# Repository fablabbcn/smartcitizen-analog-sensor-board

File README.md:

# SmartCitizen Analog Sensor Boards

This repository contains a set of boards that can interface the Smart Citizen Kit in different ways.

The SmartCitizen ASB is an expansion board for the [Smart Citizen Kit](https://github.com/fablabbcn/smartcitizen-kit-21) that provides connectivity to analog sensors with a high precission ADS1115 via I2C, with four configurable addresses. Daisy chainable up to 4 boards (or 2 in 8ch version) - with a total of 16 analog channels.

|Variant|# of Channels|External AREF needed|ADS format|
|:-:|:-:|:-:|:-:|
|4-channel|4|Y|SMD or [shield by adafruit](https://www.adafruit.com/product/1085)|
|8-channel-step|8|N|SMD|

## Characteristics

### Operating voltage

Natively operates at 3.3V, but can use also up to 5.5V in EXT-V, and with a selectable jumper. It integrates a level-shifter from the GROVE connector's voltage to EXT-V.

### Connectivity

I2C, from 3.3V up to 5.5V.

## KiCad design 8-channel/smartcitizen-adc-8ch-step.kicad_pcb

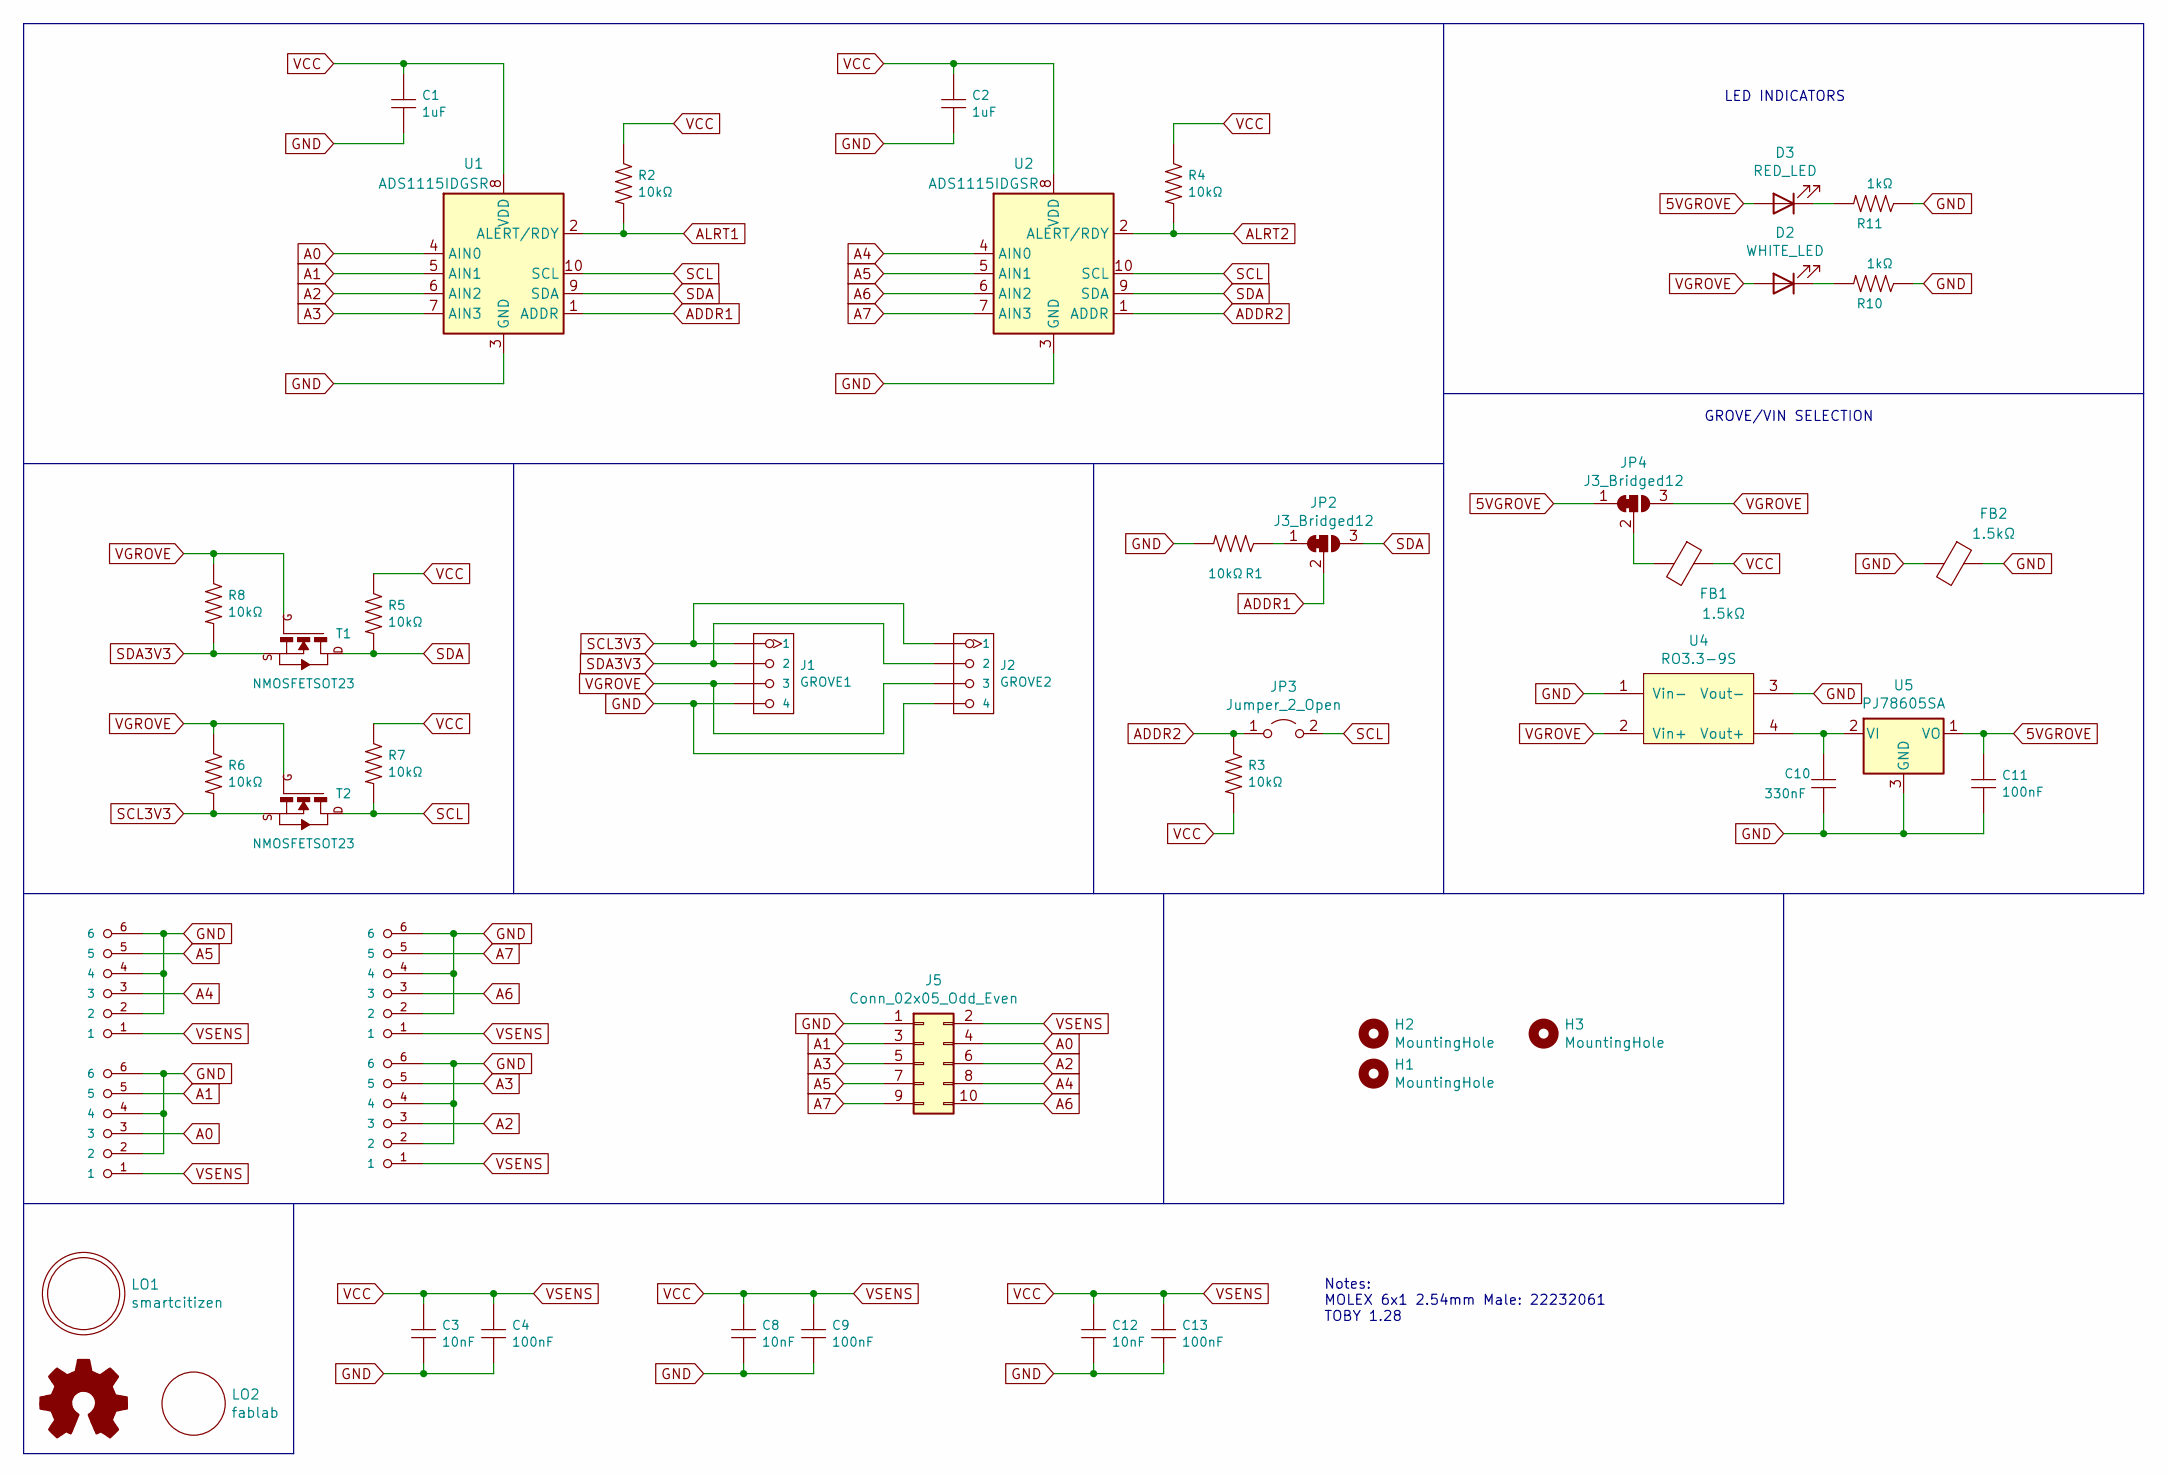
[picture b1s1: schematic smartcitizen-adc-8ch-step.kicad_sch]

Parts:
C1, C2: 1uF; C_0805_2012Metric; MFR.Part # CL21B105KBFNNNE; LCSC C28323
C3, C8, C12: 10nF; C_0805_2012Metric_Pad1.18x1.45mm_HandSolder; MFR.Part # CC0805KRX7R0BB103; LCSC C107135
C4, C9, C13: 100nF; C_0805_2012Metric_Pad1.18x1.45mm_HandSolder; MFR.Part # CC0805JRX7R9BB104; LCSC C111492
C10: 330nF; fab-C1206FAB; MFR.Part # CL31B334KBFNNNE; LCSC C307572
C11: 100nF; fab-C1206FAB; MFR.Part # CL31B104KBCNNNC; LCSC C24497
D2: WHITE_LED; LED_0402_1005Metric; MFR.Part # BL-HZ337A-L6-TRB; LCSC C189305
D3: RED_LED; LED_0402_1005Metric; MFR.Part # 2SA0402S11A0JT01; LCSC C233194
FB1, FB2: 1.5kΩ; R_0805_2012Metric_Pad1.20x1.40mm_HandSolder; MFR.Part # MMZ2012Y152B; LCSC C21517
H1, H2, H3: MountingHole; MountingHole_3.2mm_M3
J1: GROVE1; HW4-SMD-2.0-90D
J2: GROVE2; HW4-SMD-2.0-90D
J5: Conn_02x05_Odd_Even; PinSocket_2x05_P2.00mm_Vertical
JP2, JP4: J3_Bridged12; SolderJumper-3_P1.3mm_Bridged12_RoundedPad1.0x1.5mm
JP3: Jumper_2_Open; SolderJumper-2_P1.3mm_Open_RoundedPad1.0x1.5mm
LO1: smartcitizen
LO2: fablab
M1, M2, M3, M4: PINHD-1x06-HEADER; Molex_KK-254_AE-6410-06A_1x06_P2.54mm_Vertical
OSH1: Logo_Open_Hardware_Small; OSHW-Symbol_6.7x6mm_SilkScreen
R1, R2, R3, R4, R5, R6, R7, R8: 10kΩ; R_0603_1608Metric; MFR.Part # 0603WAF1002T5E; LCSC C25804
R10, R11: 1kΩ; R_0402_1005Metric; MFR.Part # 0402WGF1001TCE; LCSC C11702
T1, T2: NMOSFETSOT23; fab-SOT-23; MFR.Part # SI2310; LCSC C431497
U1, U2: ADS1115IDGSR; TSSOP-10_3x3mm_P0.5mm; MFR.Part # ADS1115IDGSR; LCSC C37593
U4: RO3.3-9S; Converter_DCDC_RECOM_RO_3.309S
U5: PJ78605SA; SOT-23; LCSC C411751

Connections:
5VGROVE: C11.1, D3.2 (A), JP4.1 (A), U5.1 (VO)
A0: J5.4, M2.3, U1.4 (AIN0)
A1: J5.3, M2.5, U1.5 (AIN1)
A2: J5.6, M4.3, U1.6 (AIN2)
A3: J5.5, M4.5, U1.7 (AIN3)
A4: J5.8, M1.3, U2.4 (AIN0)
A5: J5.7, M1.5, U2.5 (AIN1)
A6: J5.10, M3.3, U2.6 (AIN2)
A7: J5.9, M3.5, U2.7 (AIN3)
ADDR1: JP2.2 (C), U1.1 (ADDR)
ADDR2: JP3.1 (A), R3.1, U2.1 (ADDR)
ALRT1: R2.2, U1.2 (ALERT/RDY)
ALRT2: R4.2, U2.2 (ALERT/RDY)
GND: C1.2, C2.2, C3.2, C4.2, C8.2, C9.2, C10.2, C11.2, C12.2, C13.2, FB2.1, FB2.2, J1.4, J2.4, J5.1, M1.2, M1.4, M1.6, M2.2, M2.4, M2.6, M3.2, M3.4, M3.6, M4.2, M4.4, M4.6, R1.2, R10.1, R11.1, U1.3 (GND), U2.3 (GND), U4.1 (Vin-), U4.3 (Vout-), U5.3 (GND)
unnamed: C10.1, U4.4 (Vout+), U5.2 (VI)
unnamed: D2.1 (K), R10.2
unnamed: D3.1 (K), R11.2
unnamed: FB1.2, JP4.2 (C)
unnamed: JP2.1 (A), R1.1
SCL: JP3.2 (B), R7.2, T2.1 (D), U1.10 (SCL), U2.10 (SCL)
SCL3V3: J1.1, J2.1, R6.2, T2.2 (S)
SDA: JP2.3 (B), R5.2, T1.1 (D), U1.9 (SDA), U2.9 (SDA)
SDA3V3: J1.2, J2.2, R8.2, T1.2 (S)
VCC: C1.1, C2.1, C3.1, C4.1, C8.1, C9.1, C12.1, C13.1, FB1.1, J5.2, M1.1, M2.1, M3.1, M4.1, R2.1, R3.2, R4.1, R5.1, R7.1, U1.8 (VDD), U2.8 (VDD)
VGROVE: D2.2 (A), J1.3, J2.3, JP4.3 (B), R6.1, R8.1, T1.3 (G), T2.3 (G), U4.2 (Vin+)

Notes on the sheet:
LED INDICATORS
Notes: MOLEX 6x1 2.54mm Male: 22232061 TOBY 1.28
GROVE/VIN SELECTION

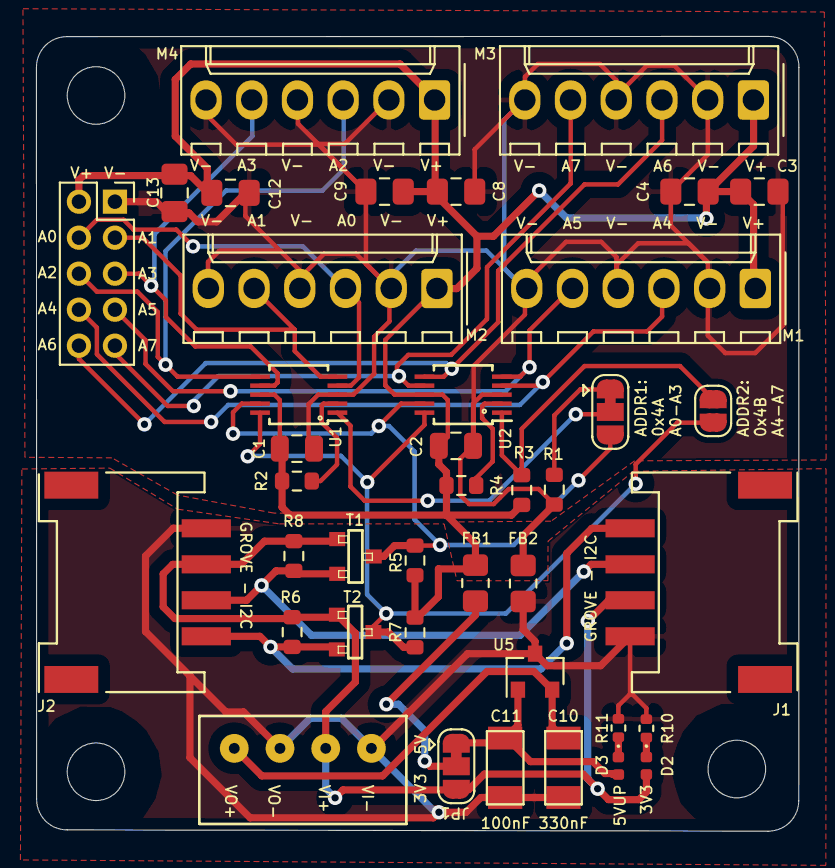
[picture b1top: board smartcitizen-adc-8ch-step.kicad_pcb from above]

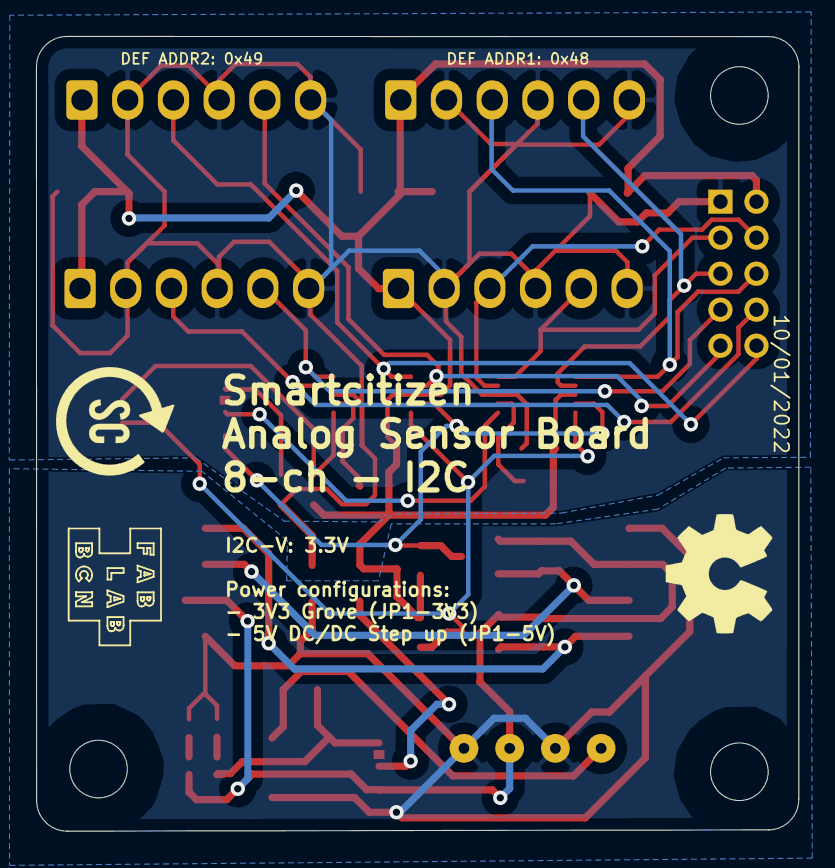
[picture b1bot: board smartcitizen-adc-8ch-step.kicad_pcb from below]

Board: 2 copper layers, 42.4 x 44.1 mm, 46 parts (3 on the bottom side), 25 nets.

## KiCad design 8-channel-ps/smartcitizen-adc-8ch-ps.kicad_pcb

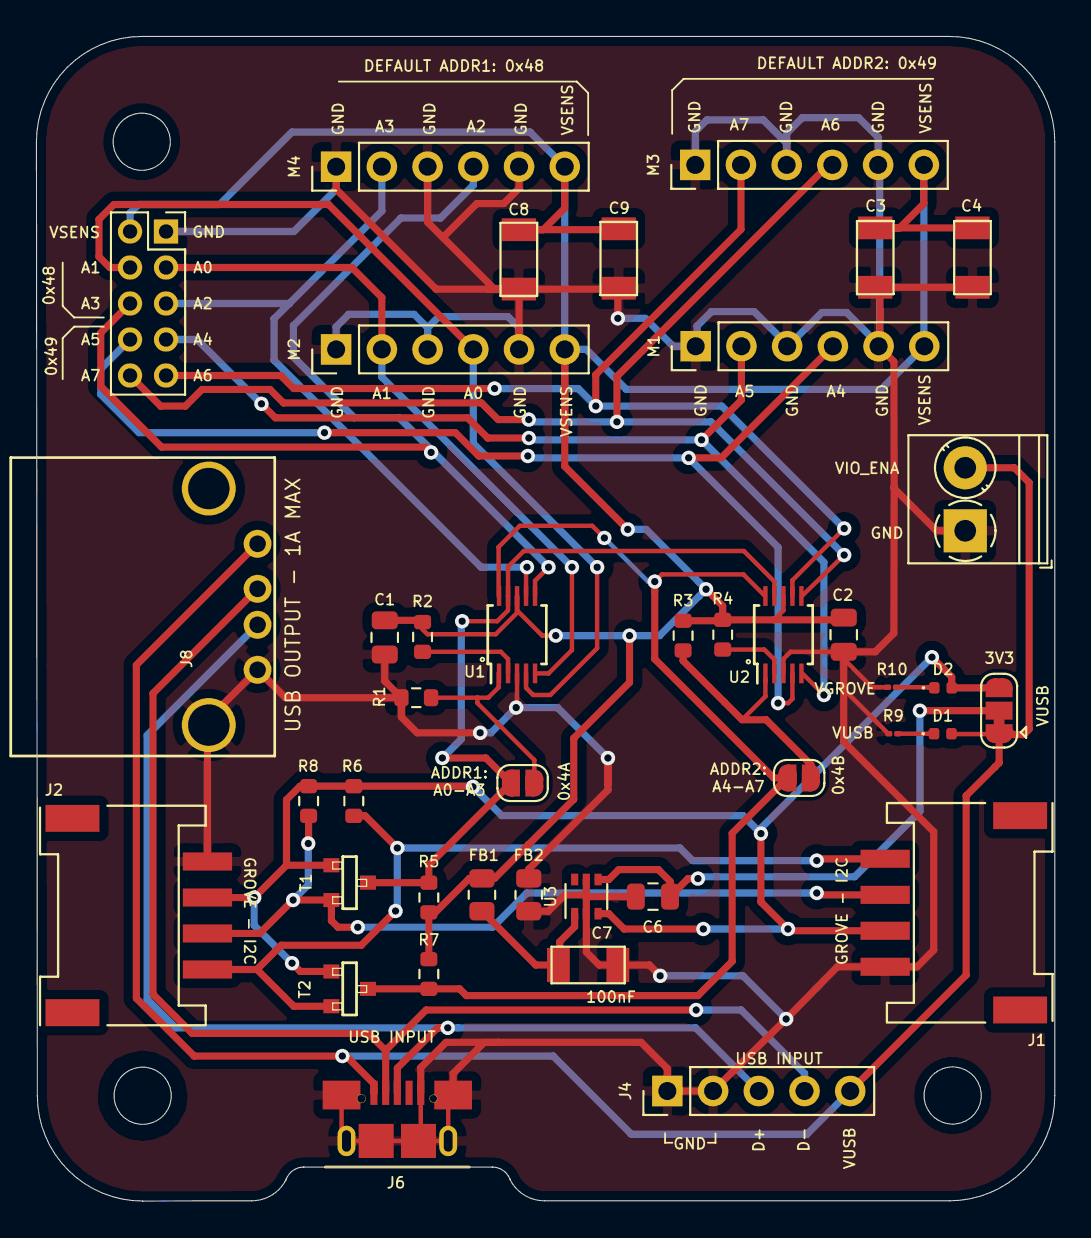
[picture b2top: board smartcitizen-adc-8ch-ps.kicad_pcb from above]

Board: 2 copper layers, 56.6 x 64.7 mm, 41 parts (0 on the bottom side), 26 nets.

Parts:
C1, C2, C6: 1uF; C_0805_2012Metric
C3, C8: 10nF; fab-C1206FAB
C4, C7, C9: 100nF; fab-C1206FAB
D1: RED_LED; LED_0402_1005Metric
D2: WHITE_LED; LED_0402_1005Metric
FB1, FB2: 1.5kΩ; R_0805_2012Metric
J1: GROVE1; HW4-SMD-2.0-90D
J2: GROVE2; HW4-SMD-2.0-90D
J3: VIN; TerminalBlock_Phoenix_PT-1,5-2-3.5-H_1x02_P3.50mm_Horizontal
J4: USB_BULGIN; PinHeader_1x05_P2.54mm_Vertical
J5: Conn_02x05_Odd_Even; PinSocket_2x05_P2.00mm_Vertical
J6: USB_B_Micro; USB_Micro-B_XKB-U254-051T-4BH83-F1S_Horizontal
J8: USB_A; USB_A_Amphenol_87520-1110BLF
JP1: J3_Bridged12; SolderJumper-3_P1.3mm_Bridged12_RoundedPad1.0x1.5mm
JP2, JP3: Jumper_2_Open; SolderJumper-2_P1.3mm_Open_RoundedPad1.0x1.5mm
M1, M2, M3, M4: PINHD-1x06-HEADER; PinHeader_1x06_P2.54mm_Vertical
R1, R2, R3, R4, R5, R6, R7, R8: 10kΩ; R_0603_1608Metric
R9, R10: 1kΩ; R_01005_0402Metric
T1, T2: NMOSFETSOT23; fab-SOT-23
U1, U2: ADS1115IDGSR; TSSOP-10_3x3mm_P0.5mm
U3: SiP32431DR3; SOT-363_SC-70-6

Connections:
A0: J5.4, M2.4, U1.4
A1: J5.3, M2.2, U1.5
A2: J5.6, M4.4, U1.6
A3: J5.5, M4.2, U1.7
A4: J5.8, M1.4, U2.4
A5: J5.7, M1.2, U2.5
A6: J5.10, M3.4, U2.6
A7: J5.9, M3.2, U2.7
ADDR1: JP2.1, R1.1, U1.1
ADDR2: JP3.1, R3.1, U2.1
ALRT1: R2.2, U1.2
ALRT2: R4.2, U2.2
D+: J4.3, J6.3, J8.3
D-: J4.4, J6.2, J8.2
GND: C1.2, C2.2, C3.2, C4.2, C6.2, C7.2, C8.2, C9.2, FB2.1, FB2.2, J1.4, J2.4, J3.1, J4.1, J4.2, J5.1, J6.5, J6.6, J8.4, J8.5, M1.1, M1.3, M1.5, M2.1, M2.3, M2.5, M3.1, M3.3, M3.5, M4.1, M4.3, M4.5, R1.2, R9.1, R10.1, U1.3, U2.3, U3.2, U3.5
unnamed: C7.1, FB1.2, U3.1
unnamed: D1.1, R9.2
unnamed: D2.1, R10.2
SCL: JP3.2, R7.2, T2.1, U1.10, U2.10
SCL3V3: J1.1, J2.1, R6.2, T2.2
SDA: JP2.2, R5.2, T1.1, U1.9, U2.9
SDA3V3: J1.2, J2.2, R8.2, T1.2
VCC: C1.1, C2.1, C3.1, C4.1, C8.1, C9.1, FB1.1, J5.2, M1.6, M2.6, M3.6, M4.6, R2.1, R3.2, R4.1, R5.1, R7.1, U1.8, U2.8
VCC_PRE: C6.1, JP1.2, U3.4
VGROVE: D2.2, J1.3, J2.3, JP1.3, R6.1, R8.1, T1.3, T2.3, U3.3
VUSB: D1.2, J3.2, J4.5, J6.1, J8.1, JP1.1

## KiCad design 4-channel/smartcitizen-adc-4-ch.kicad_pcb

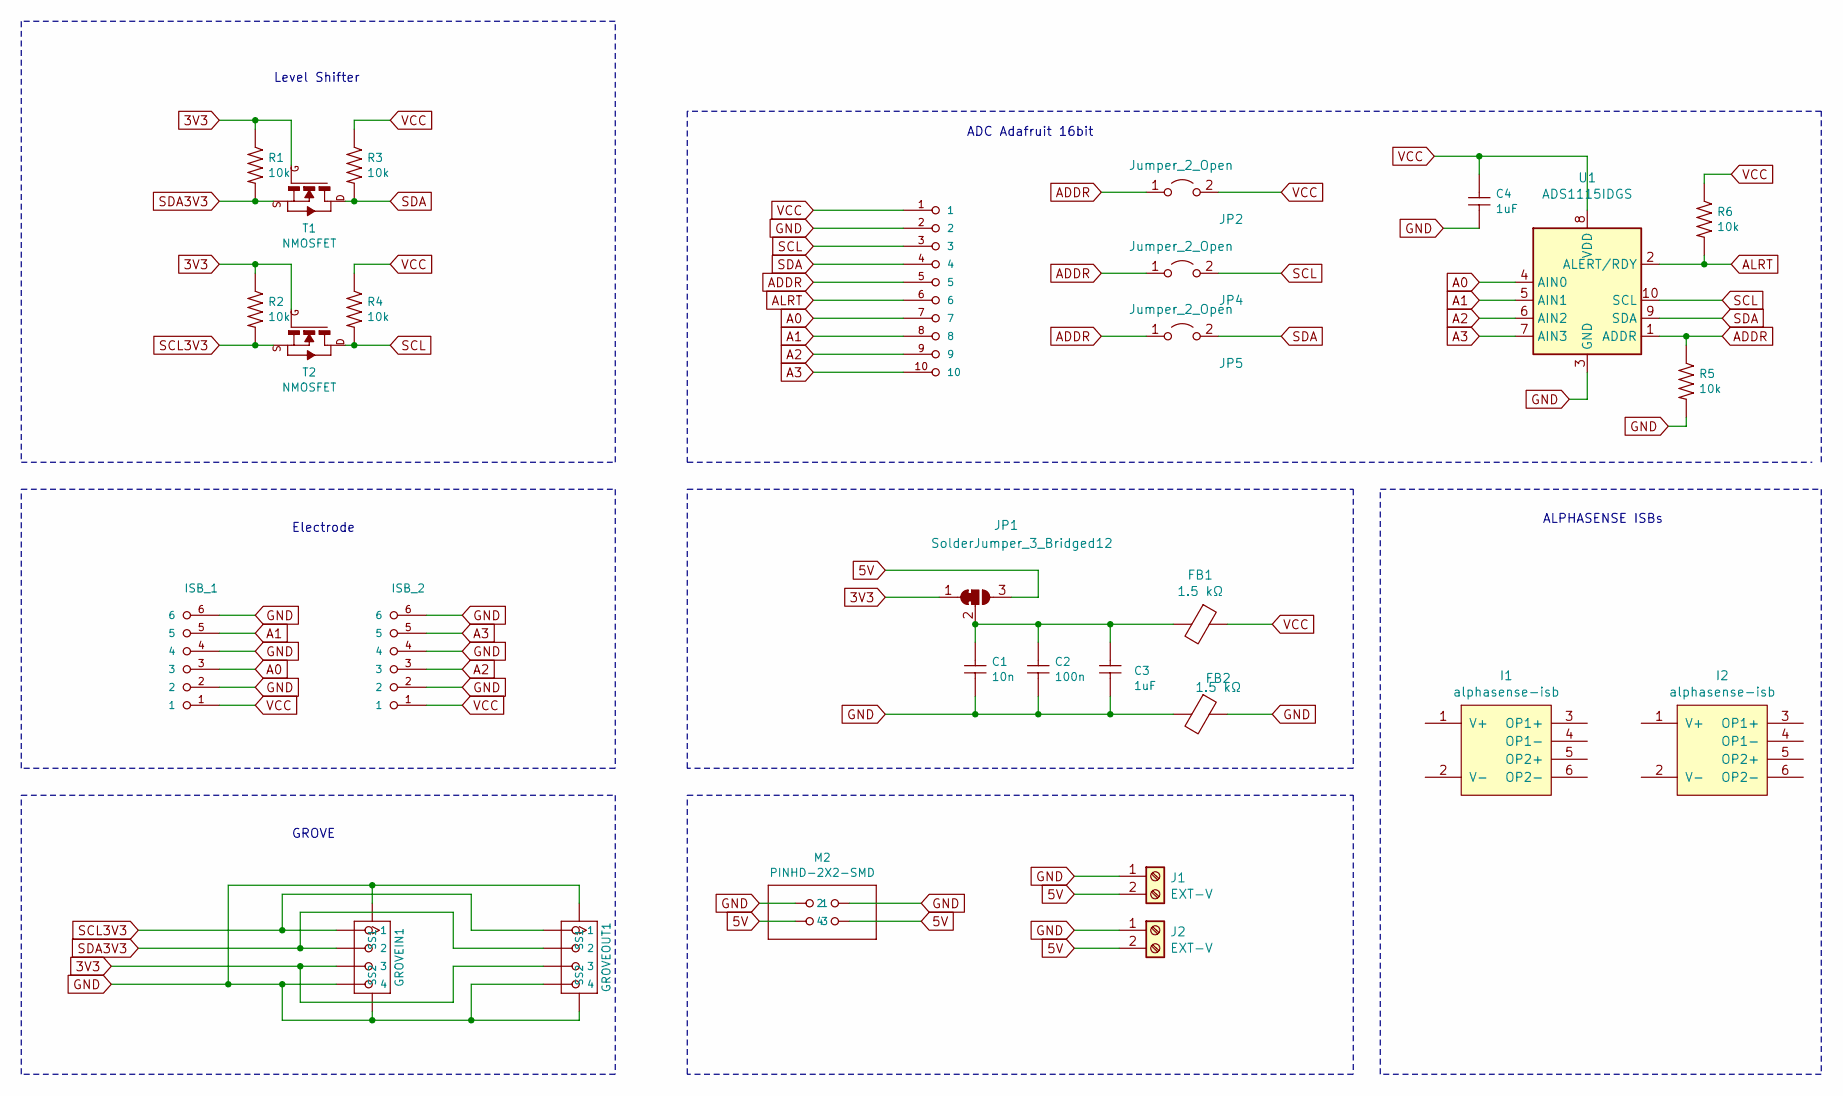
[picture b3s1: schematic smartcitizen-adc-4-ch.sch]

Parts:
C1: 10n; fab-C1206FAB; LCSC C1944
C2: 100n; fab-C1206FAB; LCSC C24497
C3, C4: 1uF; fab-C1206FAB; LCSC C1848
FB1, FB2: 1.5 kΩ; fab-R1206FAB; LCSC C21517
GROVEIN1: GROVE-CONNECTOR-SMD-90D_4+2P-2.0_; HW4-SMD-2.0-90D
GROVEOUT1: GROVE-CONNECTOR-DIP_4P-2.0_; HW4-SMD-2.0-90D
I1, I2: alphasense-isb
ISB_1, ISB_2: PINHD-1x06-HEADER; fab-1X06
J1, J2: EXT-V; TerminalBlock_Phoenix_PT-1,5-2-3.5-H_1x02_P3.50mm_Horizontal
JP1: SolderJumper_3_Bridged12; SolderJumper-3_P1.3mm_Bridged12_RoundedPad1.0x1.5mm_NumberL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
JP2, JP4, JP5: Jumper_2_Open; SolderJumper-2_P1.3mm_Open_RoundedPad1.0x1.5mm
M1: PINHD-1x10-HEADER; ads11x5
M2: PINHD-2X2-SMD; fab-2X02SMD
R1, R2, R3, R4, R5, R6: 10k; fab-R1206FAB; LCSC C17902
T1: NMOSFET; fab-SOT-23; LCSC C431497
T2: NMOSFET; fab-SOT-23; LCSC NCE2304
U1: ADS1115IDGS; TSSOP-10_3x3mm_P0.5mm; LCSC C37593

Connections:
3V3: GROVEIN1.3, GROVEOUT1.3, JP1.1 (A), R1.1, R2.1, T1.3 (G), T2.3 (G)
5V: J1.2, J2.2, JP1.3 (B), M2.3, M2.4
A0: ISB_1.3, M1.7, U1.4 (AIN0)
A1: ISB_1.5, M1.8, U1.5 (AIN1)
A2: ISB_2.3, M1.9, U1.6 (AIN2)
A3: ISB_2.5, M1.10, U1.7 (AIN3)
ADDR: JP2.1 (A), JP4.1 (A), JP5.1 (A), M1.5, R5.1, U1.1 (ADDR)
ALRT: M1.6, R6.2, U1.2 (ALERT/RDY)
GND: C1.2, C2.2, C3.2, C4.2, FB2.1, FB2.2, GROVEIN1.4, GROVEIN1.5 (SS1), GROVEIN1.6 (SS2), GROVEOUT1.4, GROVEOUT1.5 (SS1), GROVEOUT1.6 (SS2), ISB_1.2, ISB_1.4, ISB_1.6, ISB_2.2, ISB_2.4, ISB_2.6, J1.1, J2.1, M1.2, M2.1, M2.2, R5.2, U1.3 (GND)
unnamed: C1.1, C2.1, C3.1, FB1.2, JP1.2 (C)
SCL: JP4.2 (B), M1.3, R4.2, T2.1 (D), U1.10 (SCL)
SCL3V3: GROVEIN1.1, GROVEOUT1.1, R2.2, T2.2 (S)
SDA: JP5.2 (B), M1.4, R3.2, T1.1 (D), U1.9 (SDA)
SDA3V3: GROVEIN1.2, GROVEOUT1.2, R1.2, T1.2 (S)
VCC: C4.1, FB1.1, ISB_1.1, ISB_2.1, JP2.2 (B), M1.1, R3.1, R4.1, R6.1, U1.8 (VDD)

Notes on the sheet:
Level Shifter
ADC Adafruit 16bit
Electrode
GROVE
ALPHASENSE ISBs

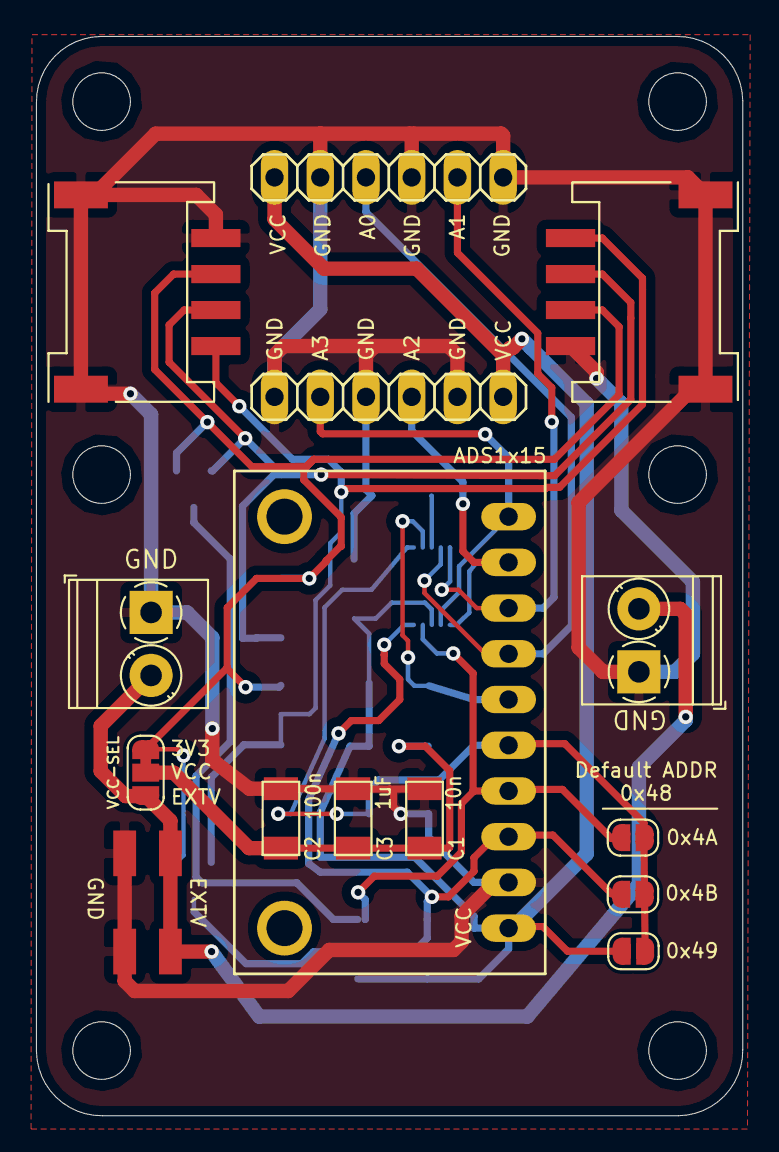
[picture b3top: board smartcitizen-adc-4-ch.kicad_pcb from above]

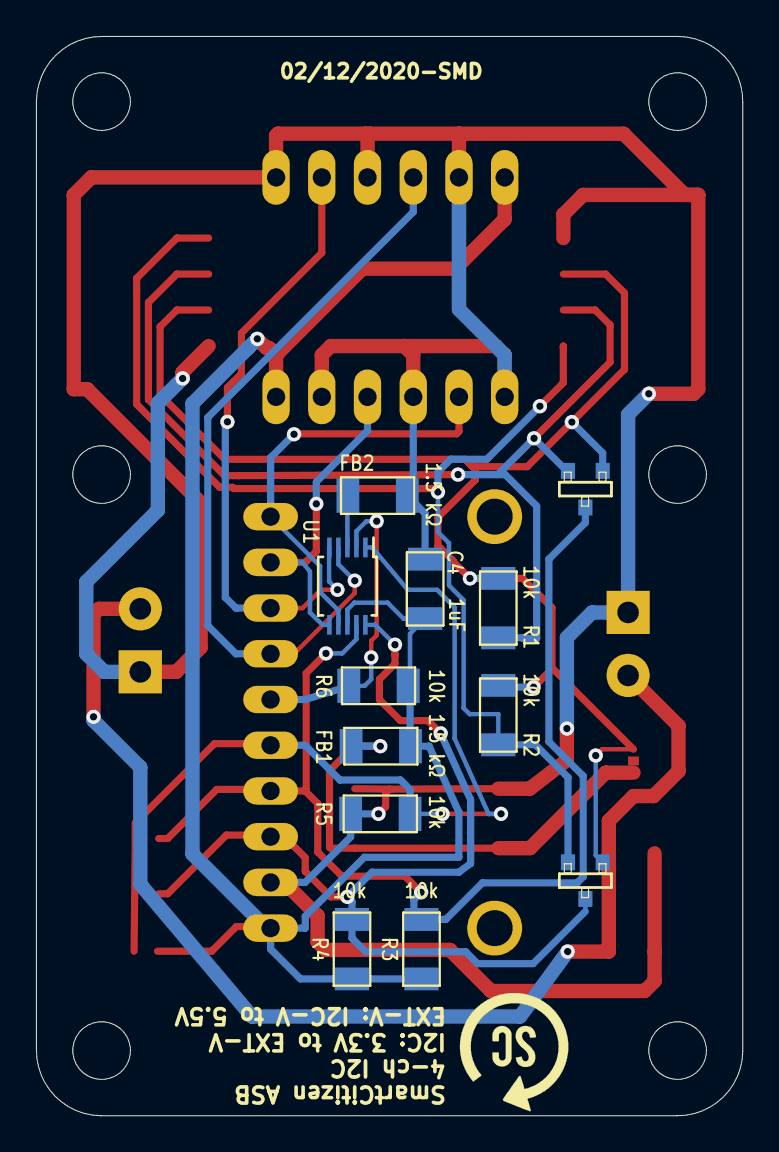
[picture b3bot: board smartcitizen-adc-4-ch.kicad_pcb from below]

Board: 2 copper layers, 39.2 x 60.0 mm, 27 parts (12 on the bottom side), 15 nets.

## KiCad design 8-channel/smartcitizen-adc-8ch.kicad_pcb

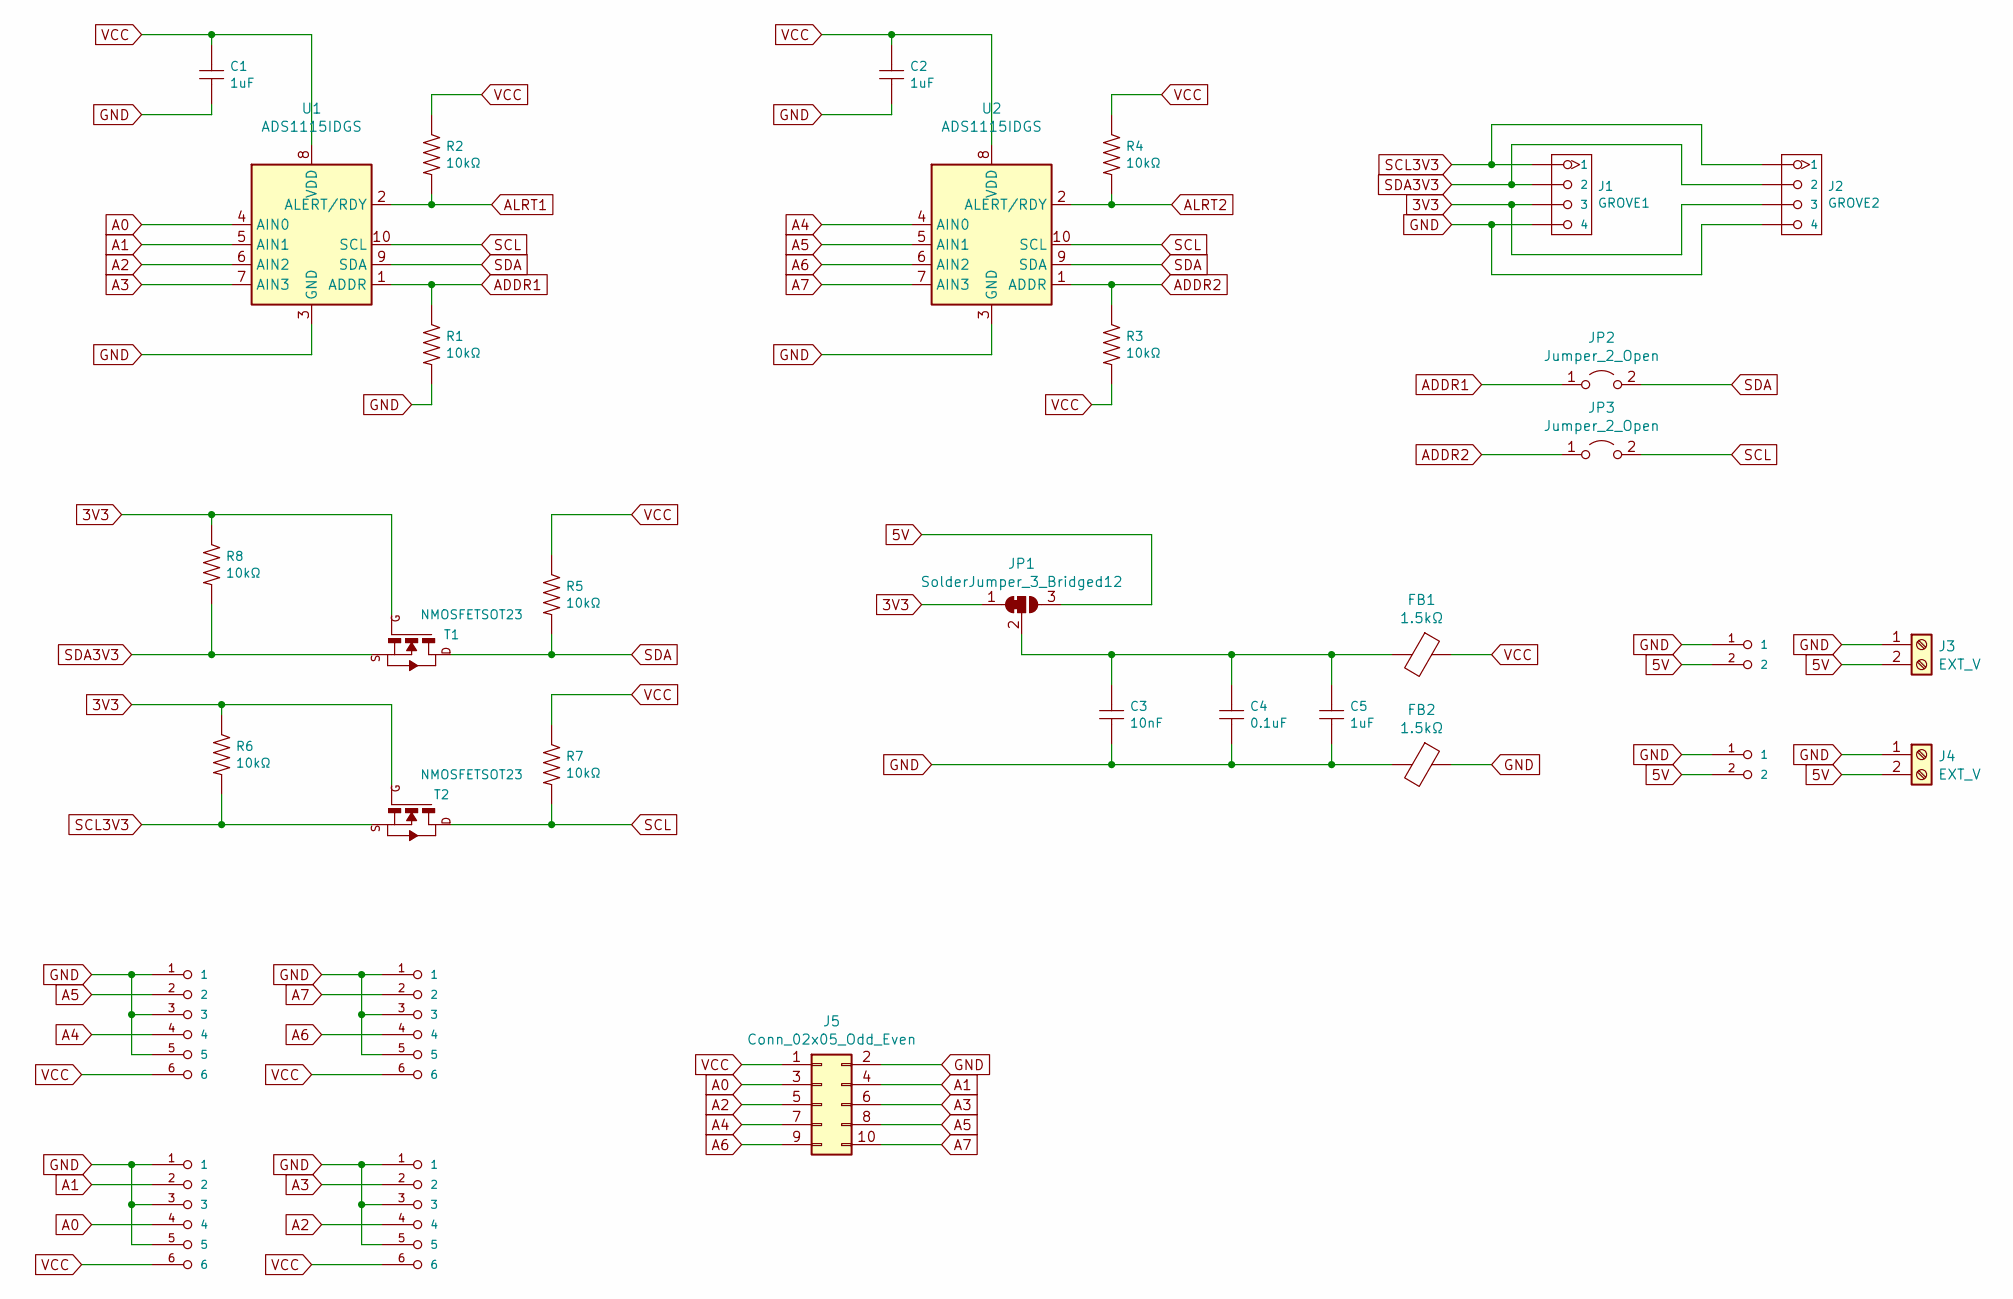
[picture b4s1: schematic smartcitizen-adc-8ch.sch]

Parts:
C1, C2, C5: 1uF; fab-C1206FAB
C3: 10nF; fab-C1206FAB
C4: 0.1uF; fab-C1206FAB
FB1, FB2: 1.5kΩ; fab-C1206FAB
J1: GROVE1; HW4-2.0
J2: GROVE2; HW4-2.0
J3, J4: EXT_V; TerminalBlock_Phoenix_PT-1,5-2-3.5-H_1x02_P3.50mm_Horizontal
J5: Conn_02x05_Odd_Even; PinSocket_2x05_P2.00mm_Vertical
JP1: SolderJumper_3_Bridged12; SolderJumper-3_P1.3mm_Bridged12_RoundedPad1.0x1.5mm
JP2, JP3: Jumper_2_Open; SolderJumper-2_P1.3mm_Open_RoundedPad1.0x1.5mm
M1, M2, M3, M4: PINHD-1x06-HEADER; fab-1X06
M5, M6: PINHD-1x02-HEADER; fab-1X02
R1, R2, R3, R4, R5, R6, R7, R8: 10kΩ; fab-R1206FAB
T1, T2: NMOSFETSOT23; fab-SOT-23
U1, U2: ADS1115IDGS; TSSOP-10_3x3mm_P0.5mm

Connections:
3V3: J1.3, J2.3, JP1.1 (A), R6.1, R8.1, T1.3 (G), T2.3 (G)
5V: J3.2, J4.2, JP1.3 (B), M5.2, M6.2
A0: J5.3, M2.4, U1.4 (AIN0)
A1: J5.4, M2.2, U1.5 (AIN1)
A2: J5.5, M4.4, U1.6 (AIN2)
A3: J5.6, M4.2, U1.7 (AIN3)
A4: J5.7, M1.4, U2.4 (AIN0)
A5: J5.8, M1.2, U2.5 (AIN1)
A6: J5.9, M3.4, U2.6 (AIN2)
A7: J5.10, M3.2, U2.7 (AIN3)
ADDR1: JP2.1 (A), R1.1, U1.1 (ADDR)
ADDR2: JP3.1 (A), R3.1, U2.1 (ADDR)
ALRT1: R2.2, U1.2 (ALERT/RDY)
ALRT2: R4.2, U2.2 (ALERT/RDY)
GND: C1.2, C2.2, C3.2, C4.2, C5.2, FB2.1, FB2.2, J1.4, J2.4, J3.1, J4.1, J5.2, M1.1, M1.3, M1.5, M2.1, M2.3, M2.5, M3.1, M3.3, M3.5, M4.1, M4.3, M4.5, M5.1, M6.1, R1.2, U1.3 (GND), U2.3 (GND)
unnamed: C3.1, C4.1, C5.1, FB1.2, JP1.2 (C)
SCL: JP3.2 (B), R7.2, T2.1 (D), U1.10 (SCL), U2.10 (SCL)
SCL3V3: J1.1, J2.1, R6.2, T2.2 (S)
SDA: JP2.2 (B), R5.2, T1.1 (D), U1.9 (SDA), U2.9 (SDA)
SDA3V3: J1.2, J2.2, R8.2, T1.2 (S)
VCC: C1.1, C2.1, FB1.1, J5.1, M1.6, M2.6, M3.6, M4.6, R2.1, R3.2, R4.1, R5.1, R7.1, U1.8 (VDD), U2.8 (VDD)

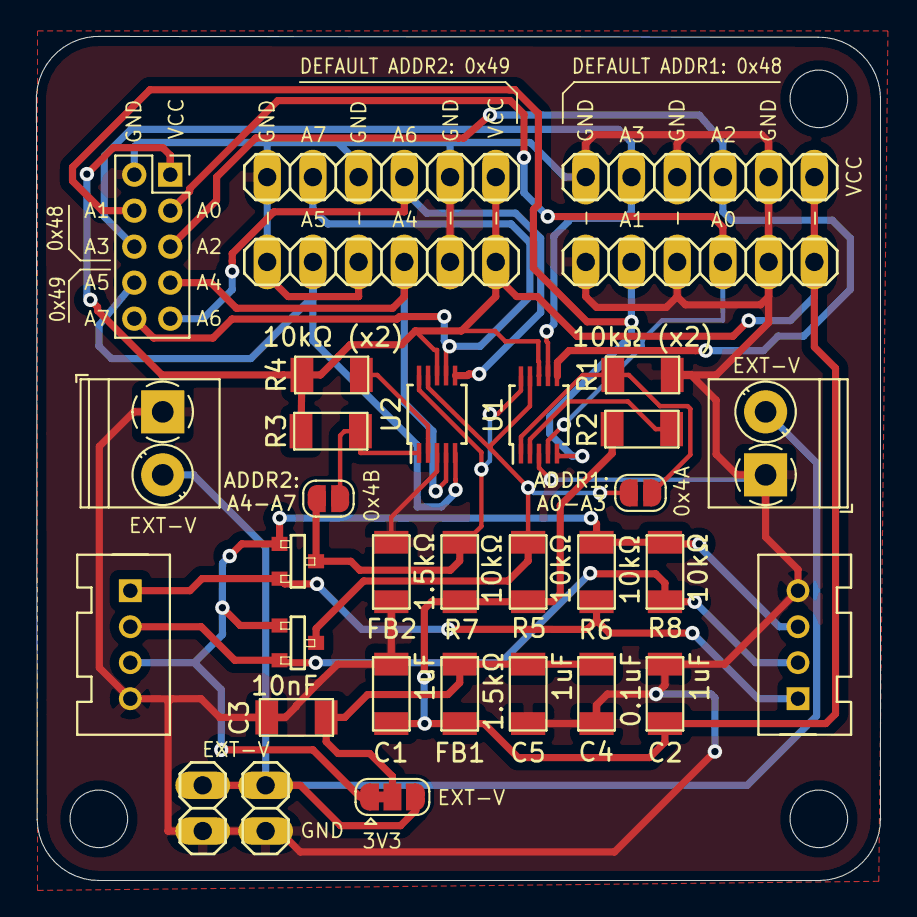
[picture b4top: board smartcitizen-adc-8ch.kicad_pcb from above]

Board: 2 copper layers, 46.9 x 46.9 mm, 33 parts (0 on the bottom side), 21 nets.

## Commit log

2020-06-30 4 channel ADC board
2020-07-01 Add 8 channel board
2020-07-06 Add gerbers
2020-07-07 4-channel exports
2020-07-07 8-channel footprint
2020-07-07 4-channel on pcb version
2020-11-11 Add photo
2020-12-22 Move traces out of screw, move components to bottom layer for SMD
2021-04-15 Add 8-ch USB version
2021-05-29 Add 8-channel version
2021-06-13 Add reduced 8-channel step-up version
2021-07-10 Stable version fixing address issue
2021-10-13 Update gitignore
2021-10-13 Update to new 8-channel board
2022-01-31 8-channel board changes and schematic
2023-07-11 Fix missing symbols
